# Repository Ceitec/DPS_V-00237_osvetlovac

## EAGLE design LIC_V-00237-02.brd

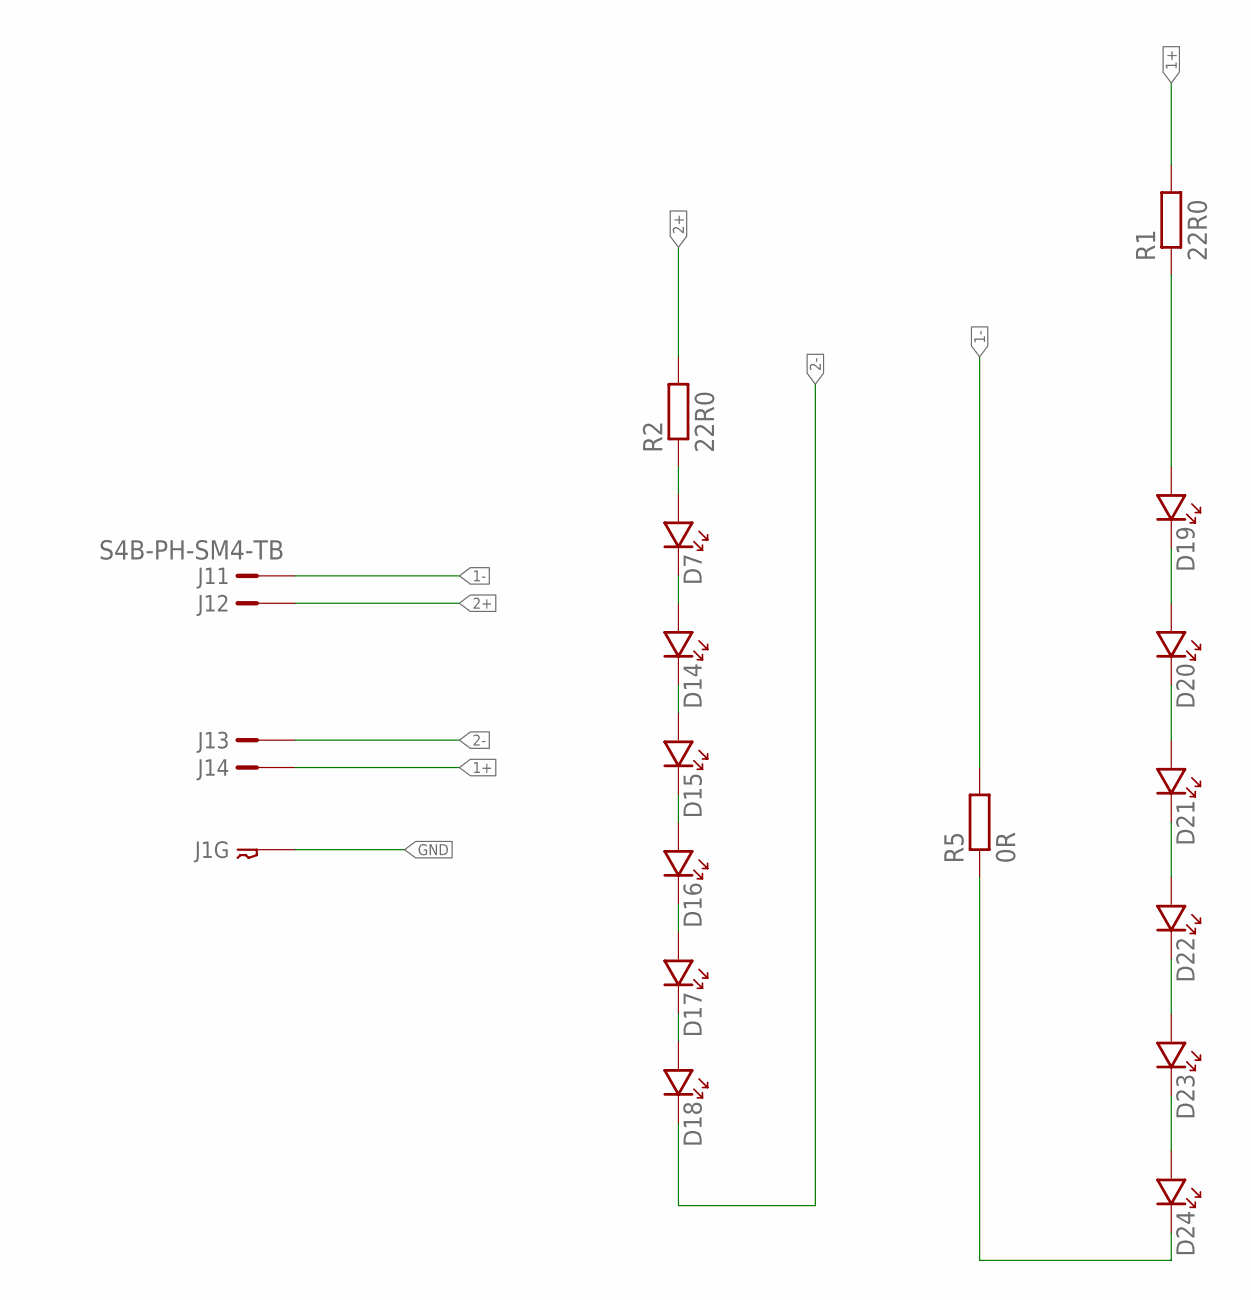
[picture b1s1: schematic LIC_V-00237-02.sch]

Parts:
D7, D14, D15, D16, D17, D18, D19, D20, D21, D22, D23, D24: LED_1206; P1206
J1: S4B-PH-SM4-TB
R1, R2: 22R0; R1206
R5: 0R; R1206

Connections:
1+: J1.4, R1.2
1-: J1.1, R5.2
2+: J1.2, R2.2
2-: D18.K, J1.3
GND: J1.GND1, J1.GND2
unnamed: D7.K, D14.A
unnamed: D14.K, D15.A
unnamed: D15.K, D16.A
unnamed: D16.K, D17.A
unnamed: D17.K, D18.A
unnamed: D7.A, R2.1
unnamed: D19.K, D20.A
unnamed: D20.K, D21.A
unnamed: D21.K, D22.A
unnamed: D22.K, D23.A
unnamed: D19.A, R1.1
unnamed: D24.K, R5.1
unnamed: D23.K, D24.A

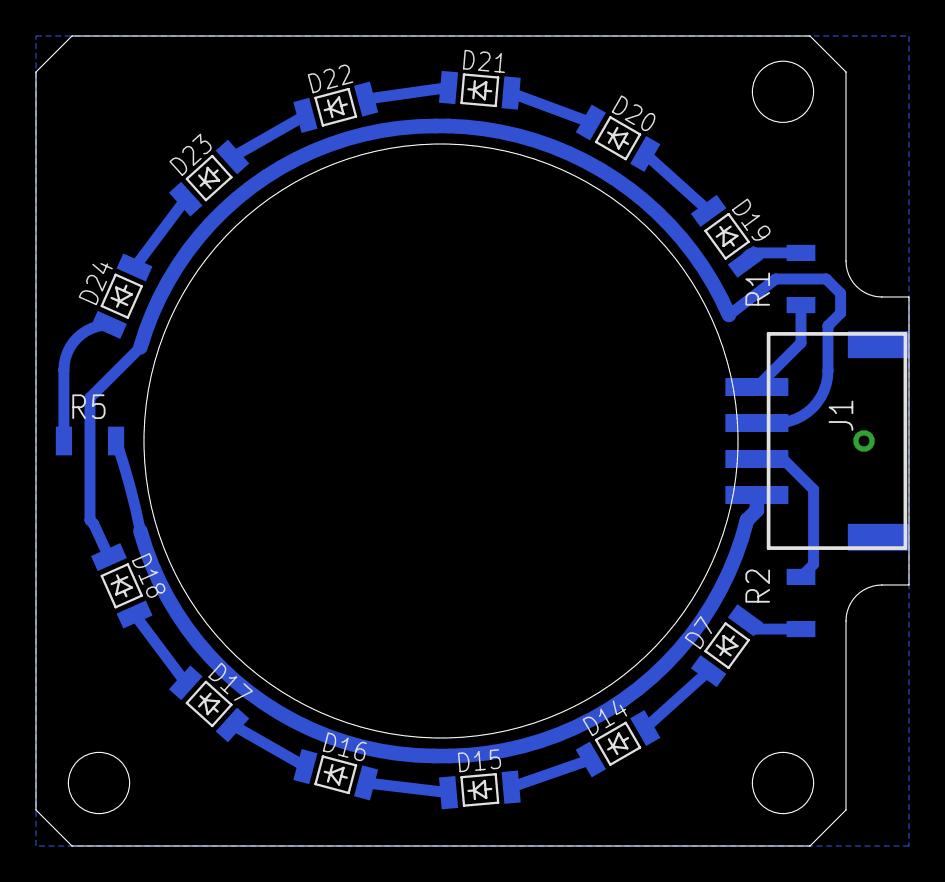
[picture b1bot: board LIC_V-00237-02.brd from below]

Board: 2 copper layers, 48.5 x 45.0 mm, 16 parts (16 on the bottom side), 18 nets.

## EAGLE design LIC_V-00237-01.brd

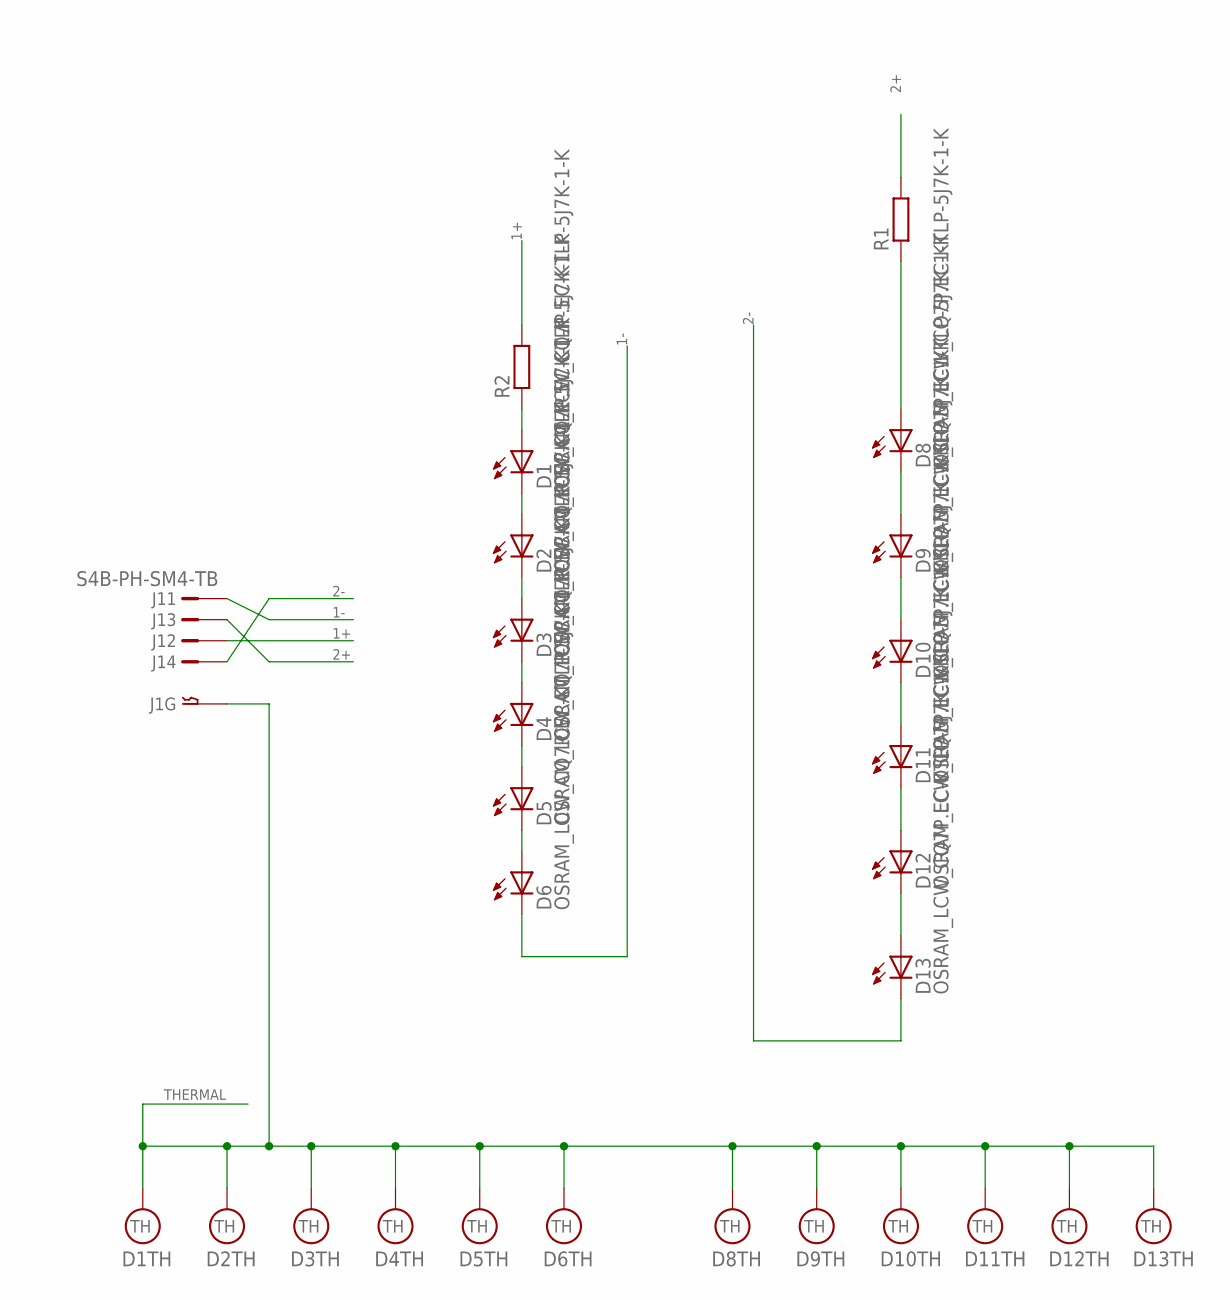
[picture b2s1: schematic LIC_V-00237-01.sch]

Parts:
D1, D2, D3, D4, D5, D6, D8, D9, D10, D11, D12, D13: OSRAM_LCW_CQ7P.EC-KTLP-5J7K-1-K; OSRAM_LCW
J1: S4B-PH-SM4-TB
R1, R2: R-EU_R1206; R1206

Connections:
1+: J1.2, R2.2
1-: D6.C, J1.1
2+: J1.3, R1.2
2-: D13.C, J1.4
unnamed: D1.C, D2.A
unnamed: D2.C, D3.A
unnamed: D3.C, D4.A
unnamed: D4.C, D5.A
unnamed: D5.C, D6.A
unnamed: D1.A, R2.1
unnamed: D8.C, D9.A
unnamed: D9.C, D10.A
unnamed: D10.C, D11.A
unnamed: D11.C, D12.A
unnamed: D8.A, R1.1
unnamed: D12.C, D13.A
THERMAL: D1.THERMAL (TH), D2.THERMAL (TH), D3.THERMAL (TH), D4.THERMAL (TH), D5.THERMAL (TH), D6.THERMAL (TH), D8.THERMAL (TH), D9.THERMAL (TH), D10.THERMAL (TH), D11.THERMAL (TH), D12.THERMAL (TH), D13.THERMAL (TH), J1.GND1, J1.GND2

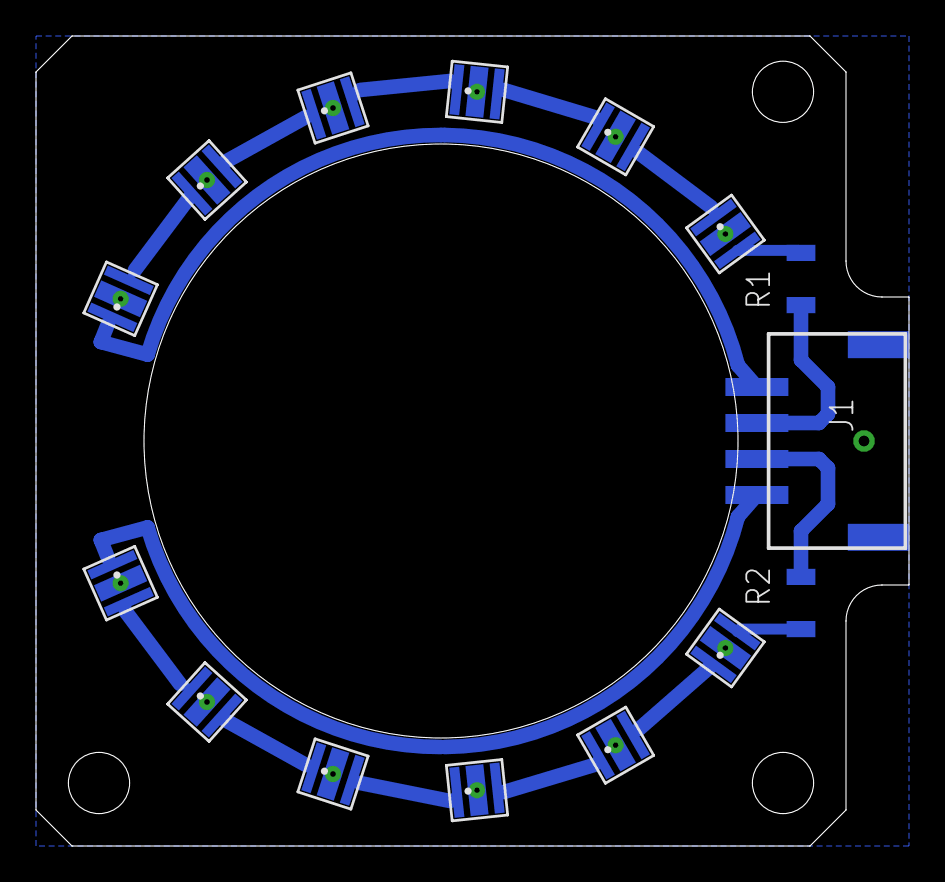
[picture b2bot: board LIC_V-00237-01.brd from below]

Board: 2 copper layers, 48.5 x 45.0 mm, 15 parts (15 on the bottom side), 17 nets.

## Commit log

2015-08-11 :circus_tent: Added .gitattributes & .gitignore files
2015-08-11 DPS pro vnitřní osvětlení
2015-11-10 Uprava další verze
    Další verze s chybou ohledně termálních plošek
2015-11-30 Další verze
    Verze pro normální LED

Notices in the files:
parts and their libraries:
Copyright (C) PaJa 2001-2014
